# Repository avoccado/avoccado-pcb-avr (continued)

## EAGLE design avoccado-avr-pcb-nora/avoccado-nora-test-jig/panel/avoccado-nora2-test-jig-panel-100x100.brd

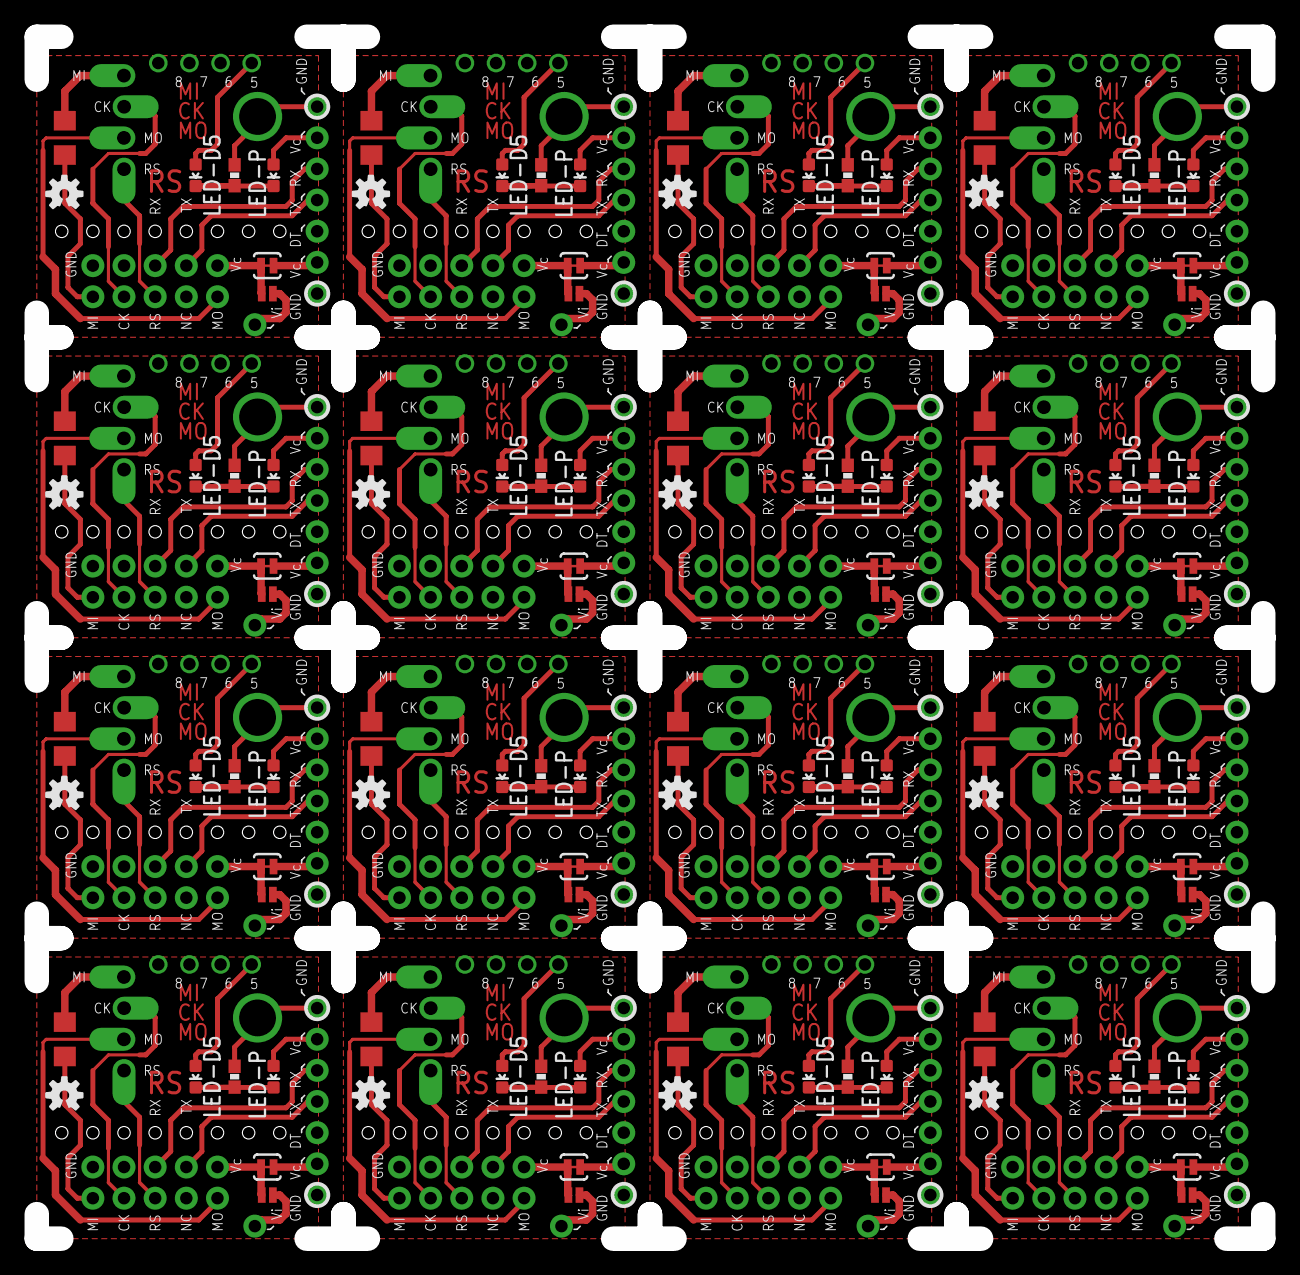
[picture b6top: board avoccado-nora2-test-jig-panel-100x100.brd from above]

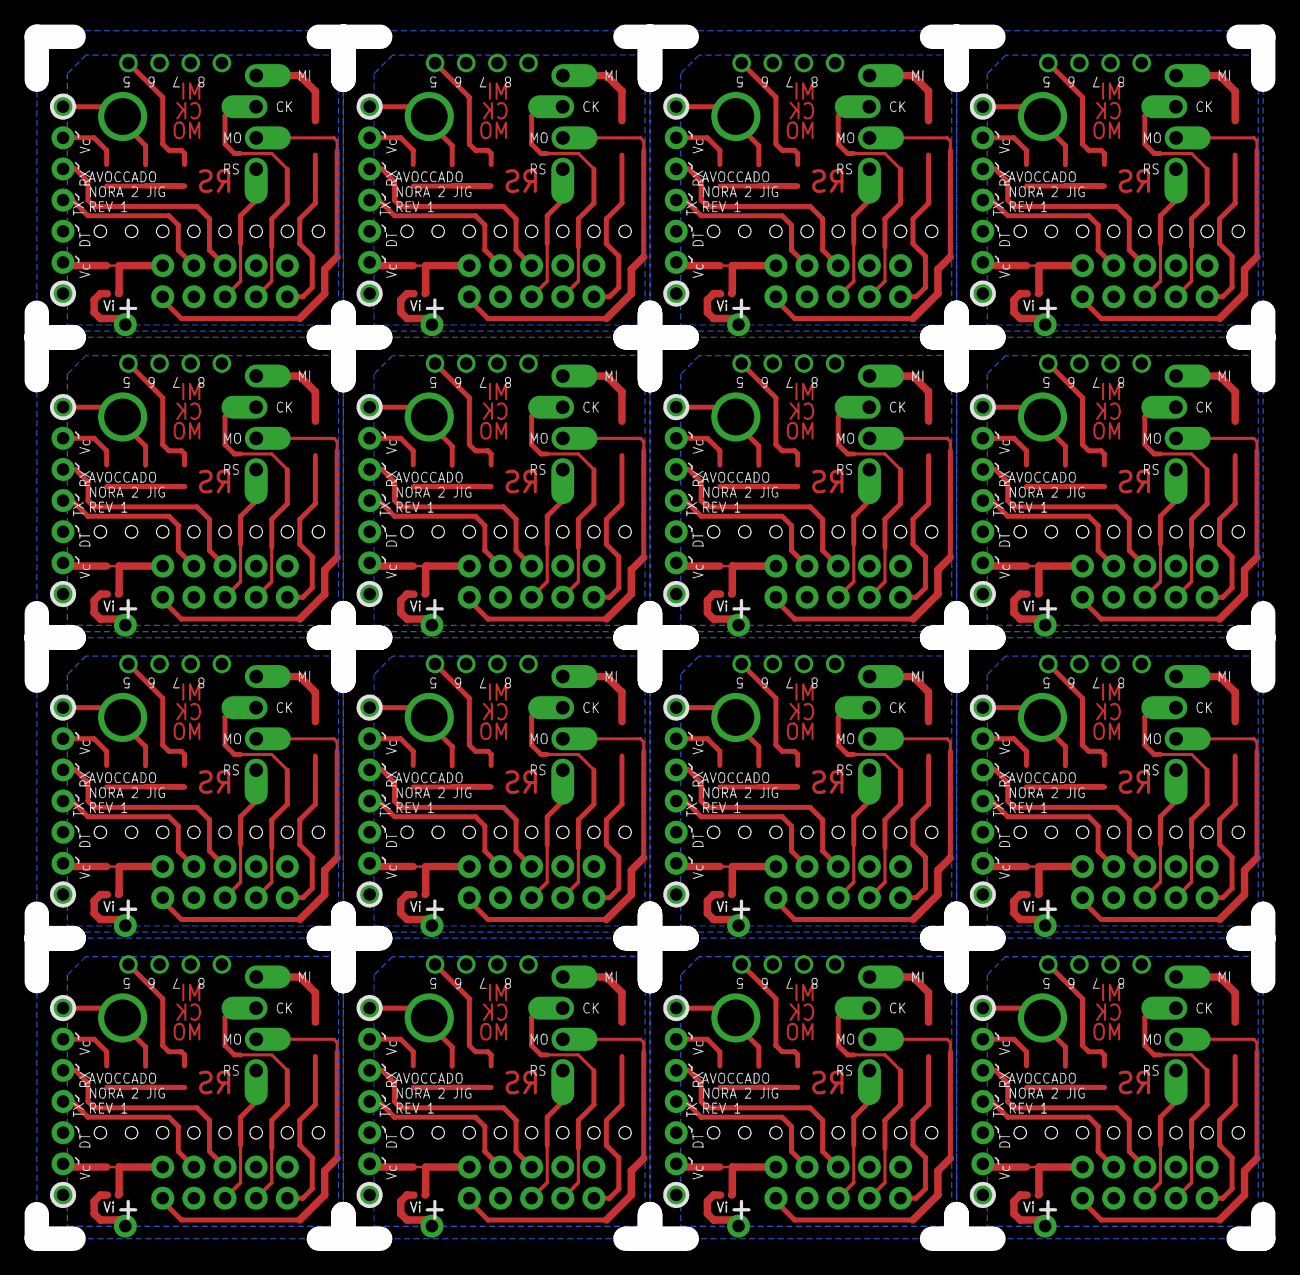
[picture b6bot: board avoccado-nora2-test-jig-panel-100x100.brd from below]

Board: 2 copper layers, 100.0 x 98.0 mm, 384 parts (16 on the bottom side), 224 nets.

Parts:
D5-LED, D5-LED1, D5-LED2, D5-LED3, D5-LED4, D5-LED5, D5-LED6, D5-LED7, D5-LED8, D5-LED9, D5-LED10, D5-LED11, D5-LED12, D5-LED13, D5-LED14, D5-LED15: LED-0603
ICSP, ICSP1, ICSP2, ICSP3, ICSP4, ICSP5, ICSP6, ICSP7, ICSP8, ICSP9, ICSP10, ICSP11, ICSP12, ICSP13, ICSP14, ICSP15: M05X2NO_SILK; 2X5_NOSILK
JP1, JP2, JP3, JP4, JP5, JP6, JP7, JP8, JP9, JP10, JP11, JP17, JP18, JP22, JP23, JP24, JP25, JP26, JP27, JP28, JP29, JP34, JP35, JP36, JP37, JP38, JP39, JP40, JP41, JP46, JP47, JP48, JP49, JP50, JP51, JP52, JP53, JP58, JP59, JP60, JP61, JP62, JP63, JP64, JP65, JP70, JP71, JP72, JP73, JP74, JP75, JP76, JP77, JP82, JP83, JP84, JP85, JP86, JP87, JP88, JP89, JP94, JP95, JP96, JP97, JP98, JP99, JP100, JP101, JP106, JP107, JP108, JP109, JP110, JP111, JP112, JP113, JP118, JP119, JP120, JP121, JP122, JP123, JP124, JP125, JP130, JP131, JP132, JP133, JP134, JP135, JP136, JP137, JP142, JP143, JP144, JP145, JP146, JP147, JP148, JP149, JP154, JP155, JP156, JP157, JP158, JP159, JP160, JP161, JP166, JP167, JP168, JP169, JP170, JP171, JP172, JP173, JP178, JP179, JP180, JP181, JP182, JP183, JP184, JP185, JP190, JP191, JP192: M01PTH; 1X01
JP12, JP13, JP14, JP15, JP16, JP19, JP20, JP21, JP30, JP31, JP32, JP33, JP42, JP43, JP44, JP45, JP54, JP55, JP56, JP57, JP66, JP67, JP68, JP69, JP78, JP79, JP80, JP81, JP90, JP91, JP92, JP93, JP102, JP103, JP104, JP105, JP114, JP115, JP116, JP117, JP126, JP127, JP128, JP129, JP138, JP139, JP140, JP141, JP150, JP151, JP152, JP153, JP162, JP163, JP164, JP165, JP174, JP175, JP176, JP177, JP186, JP187, JP188, JP189: M01OFFSET; 1X01_OFFSET
LOGO1, LOGO2, LOGO3, LOGO4, LOGO5, LOGO6, LOGO7, LOGO8, LOGO9, LOGO10, LOGO11, LOGO12, LOGO13, LOGO14, LOGO15, LOGO16: OSHW-LOGOS; OSHW-LOGO-S
PWR-LED, PWR-LED1, PWR-LED2, PWR-LED3, PWR-LED4, PWR-LED5, PWR-LED6, PWR-LED7, PWR-LED8, PWR-LED9, PWR-LED10, PWR-LED11, PWR-LED12, PWR-LED13, PWR-LED14, PWR-LED15: LED-0603
R1, R3, R5, R7, R9, R11, R13, R15, R17, R19, R21, R23, R25, R27, R29, R31: 0; 1206
R2, R4, R6, R8, R10, R12, R14, R16, R18, R20, R22, R24, R26, R28, R30, R32: 1K; 0603-RES
SJ1, SJ3, SJ5, SJ7, SJ9, SJ11, SJ13, SJ15, SJ17, SJ19, SJ21, SJ23, SJ25, SJ27, SJ29, SJ31: JUMPER-PAD-2-NC_BY_TRACE; PAD-JUMPER-2-NC_BY_TRACE_YES_SILK
SJ2, SJ4, SJ6, SJ8, SJ10, SJ12, SJ14, SJ16, SJ18, SJ20, SJ22, SJ24, SJ26, SJ28, SJ30, SJ32: JUMPER-PAD-2-NO; PAD-JUMPER-2-NO_NO_SILK
TP1, TP2, TP3, TP4, TP5, TP6, TP7, TP8, TP9, TP10, TP11, TP12, TP13, TP14, TP15, TP16, TP17, TP18, TP19, TP20, TP21, TP22, TP23, TP24, TP25, TP26, TP27, TP28, TP29, TP30, TP31, TP32, TP33, TP34, TP35, TP36, TP37, TP38, TP39, TP40, TP41, TP42, TP43, TP44, TP45, TP46, TP47, TP48, TP49, TP50, TP51, TP52, TP53, TP54, TP55, TP56, TP57, TP58, TP59, TP60, TP61, TP62, TP63, TP64: M01NOSILK-KIT; 1X01NS-KIT

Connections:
3.3V: JP18.1, SJ1.1
3.3V1: JP24.1, SJ3.1
3.3V2: JP36.1, SJ5.1
3.3V3: JP48.1, SJ7.1
3.3V4: JP60.1, SJ9.1
3.3V5: JP72.1, SJ11.1
3.3V6: JP84.1, SJ13.1
3.3V7: JP96.1, SJ15.1
3.3V8: JP108.1, SJ17.1
3.3V9: JP120.1, SJ19.1
3.3V10: JP132.1, SJ21.1
3.3V11: JP144.1, SJ23.1
3.3V12: JP156.1, SJ25.1
3.3V13: JP168.1, SJ27.1
3.3V14: JP180.1, SJ29.1
3.3V15: JP192.1, SJ31.1
5V: JP17.1, SJ2.1
5V1: JP23.1, SJ4.1
5V2: JP35.1, SJ6.1
5V3: JP47.1, SJ8.1
5V4: JP59.1, SJ10.1
5V5: JP71.1, SJ12.1
5V6: JP83.1, SJ14.1
5V7: JP95.1, SJ16.1
5V8: JP107.1, SJ18.1
5V9: JP119.1, SJ20.1
5V10: JP131.1, SJ22.1
5V11: JP143.1, SJ24.1
5V12: JP155.1, SJ26.1
5V13: JP167.1, SJ28.1
5V14: JP179.1, SJ30.1
5V15: JP191.1, SJ32.1
D2: D5-LED1.A, TP2.1
D5: D5-LED.A, TP1.1
D10: D5-LED2.A, TP9.1
D14: D5-LED3.A, TP13.1
D18: D5-LED4.A, TP17.1
D22: D5-LED5.A, TP21.1
D26: D5-LED6.A, TP25.1
D30: D5-LED7.A, TP29.1
D34: D5-LED8.A, TP33.1
D38: D5-LED9.A, TP37.1
D42: D5-LED10.A, TP41.1
D46: D5-LED11.A, TP45.1
D50: D5-LED12.A, TP49.1
D54: D5-LED13.A, TP53.1
D58: D5-LED14.A, TP57.1
D62: D5-LED15.A, TP61.1
GND: ICSP.10, JP3.1, JP6.1, R2.2
GND1: ICSP1.10, JP1.1, JP22.1, R4.2
GND2: ICSP2.10, JP25.1, JP34.1, R6.2
GND3: ICSP3.10, JP37.1, JP46.1, R8.2
GND4: ICSP4.10, JP49.1, JP58.1, R10.2
GND5: ICSP5.10, JP61.1, JP70.1, R12.2
GND6: ICSP6.10, JP73.1, JP82.1, R14.2
GND7: ICSP7.10, JP85.1, JP94.1, R16.2
GND8: ICSP8.10, JP97.1, JP106.1, R18.2
GND9: ICSP9.10, JP109.1, JP118.1, R20.2
GND10: ICSP10.10, JP121.1, JP130.1, R22.2
GND11: ICSP11.10, JP133.1, JP142.1, R24.2
GND12: ICSP12.10, JP145.1, JP154.1, R26.2
GND13: ICSP13.10, JP157.1, JP166.1, R28.2
GND14: ICSP14.10, JP169.1, JP178.1, R30.2
GND15: ICSP15.10, JP181.1, JP190.1, R32.2
MISO: JP12.1, R1.1
MISO1: ICSP.9, R1.2
MISO2: JP16.1, R3.1
MISO3: ICSP1.9, R3.2
MISO4: JP30.1, R5.1
MISO5: ICSP2.9, R5.2
MISO6: JP42.1, R7.1
MISO7: ICSP3.9, R7.2
MISO8: JP54.1, R9.1
MISO9: ICSP4.9, R9.2
MISO10: JP66.1, R11.1
MISO11: ICSP5.9, R11.2
MISO12: JP78.1, R13.1
MISO13: ICSP6.9, R13.2
MISO14: JP90.1, R15.1
MISO15: ICSP7.9, R15.2
MISO16: JP102.1, R17.1
MISO17: ICSP8.9, R17.2
MISO18: JP114.1, R19.1
MISO19: ICSP9.9, R19.2
MISO20: JP126.1, R21.1
MISO21: ICSP10.9, R21.2
MISO22: JP138.1, R23.1
MISO23: ICSP11.9, R23.2
MISO24: JP150.1, R25.1
MISO25: ICSP12.9, R25.2
MISO26: JP162.1, R27.1
MISO27: ICSP13.9, R27.2
MISO28: JP174.1, R29.1
MISO29: ICSP14.9, R29.2
MISO30: JP186.1, R31.1
MISO31: ICSP15.9, R31.2
MOSI: ICSP.1, JP14.1
MOSI1: ICSP1.1, JP20.1
MOSI2: ICSP2.1, JP32.1
MOSI3: ICSP3.1, JP44.1
MOSI4: ICSP4.1, JP56.1
MOSI5: ICSP5.1, JP68.1
MOSI6: ICSP6.1, JP80.1
MOSI7: ICSP7.1, JP92.1
MOSI8: ICSP8.1, JP104.1
MOSI9: ICSP9.1, JP116.1
MOSI10: ICSP10.1, JP128.1
MOSI11: ICSP11.1, JP140.1
MOSI12: ICSP12.1, JP152.1
MOSI13: ICSP13.1, JP164.1
MOSI14: ICSP14.1, JP176.1
MOSI15: ICSP15.1, JP188.1
unnamed: D5-LED.C, PWR-LED.C, R2.1
unnamed: JP11.1, PWR-LED.A
unnamed: D5-LED1.C, PWR-LED1.C, R4.1
unnamed: JP7.1, PWR-LED1.A
unnamed: D5-LED2.C, PWR-LED2.C, R6.1
unnamed: JP29.1, PWR-LED2.A
unnamed: D5-LED3.C, PWR-LED3.C, R8.1
unnamed: JP41.1, PWR-LED3.A
unnamed: D5-LED4.C, PWR-LED4.C, R10.1
unnamed: JP53.1, PWR-LED4.A
unnamed: D5-LED5.C, PWR-LED5.C, R12.1
unnamed: JP65.1, PWR-LED5.A
unnamed: D5-LED6.C, PWR-LED6.C, R14.1
unnamed: JP77.1, PWR-LED6.A
unnamed: D5-LED7.C, PWR-LED7.C, R16.1
unnamed: JP89.1, PWR-LED7.A
unnamed: D5-LED8.C, PWR-LED8.C, R18.1
unnamed: JP101.1, PWR-LED8.A
unnamed: D5-LED9.C, PWR-LED9.C, R20.1
unnamed: JP113.1, PWR-LED9.A
unnamed: D5-LED10.C, PWR-LED10.C, R22.1
unnamed: JP125.1, PWR-LED10.A
unnamed: D5-LED11.C, PWR-LED11.C, R24.1
unnamed: JP137.1, PWR-LED11.A
unnamed: D5-LED12.C, PWR-LED12.C, R26.1
unnamed: JP149.1, PWR-LED12.A
unnamed: D5-LED13.C, PWR-LED13.C, R28.1
unnamed: JP161.1, PWR-LED13.A
unnamed: D5-LED14.C, PWR-LED14.C, R30.1
unnamed: JP173.1, PWR-LED14.A
unnamed: D5-LED15.C, PWR-LED15.C, R32.1
unnamed: JP185.1, PWR-LED15.A
RESET: ICSP.5, JP15.1
RESET1: ICSP1.5, JP21.1
RESET2: ICSP2.5, JP33.1
RESET3: ICSP3.5, JP45.1
RESET4: ICSP4.5, JP57.1
RESET5: ICSP5.5, JP69.1
RESET6: ICSP6.5, JP81.1
RESET7: ICSP7.5, JP93.1
RESET8: ICSP8.5, JP105.1
RESET9: ICSP9.5, JP117.1
RESET10: ICSP10.5, JP129.1
RESET11: ICSP11.5, JP141.1
RESET12: ICSP12.5, JP153.1
RESET13: ICSP13.5, JP165.1
RESET14: ICSP14.5, JP177.1
RESET15: ICSP15.5, JP189.1
RXI: ICSP.6, JP8.1
RXI1: ICSP1.6, JP2.1
RXI2: ICSP2.6, JP26.1
RXI3: ICSP3.6, JP38.1
RXI4: ICSP4.6, JP50.1
RXI5: ICSP5.6, JP62.1
RXI6: ICSP6.6, JP74.1
RXI7: ICSP7.6, JP86.1
RXI8: ICSP8.6, JP98.1
RXI9: ICSP9.6, JP110.1
RXI10: ICSP10.6, JP122.1
RXI11: ICSP11.6, JP134.1
RXI12: ICSP12.6, JP146.1
RXI13: ICSP13.6, JP158.1
RXI14: ICSP14.6, JP170.1
RXI15: ICSP15.6, JP182.1
SCK: ICSP.7, JP13.1
SCK1: ICSP1.7, JP19.1
SCK2: ICSP2.7, JP31.1
SCK3: ICSP3.7, JP43.1
SCK4: ICSP4.7, JP55.1
SCK5: ICSP5.7, JP67.1
SCK6: ICSP6.7, JP79.1
SCK7: ICSP7.7, JP91.1
SCK8: ICSP8.7, JP103.1
SCK9: ICSP9.7, JP115.1
SCK10: ICSP10.7, JP127.1
SCK11: ICSP11.7, JP139.1
SCK12: ICSP12.7, JP151.1
SCK13: ICSP13.7, JP163.1
SCK14: ICSP14.7, JP175.1
SCK15: ICSP15.7, JP187.1
TXO: ICSP.4, JP9.1
TXO1: ICSP1.4, JP4.1
TXO2: ICSP2.4, JP27.1
TXO3: ICSP3.4, JP39.1
TXO4: ICSP4.4, JP51.1
TXO5: ICSP5.4, JP63.1
TXO6: ICSP6.4, JP75.1
TXO7: ICSP7.4, JP87.1
TXO8: ICSP8.4, JP99.1
TXO9: ICSP9.4, JP111.1
TXO10: ICSP10.4, JP123.1
TXO11: ICSP11.4, JP135.1
TXO12: ICSP12.4, JP147.1
TXO13: ICSP13.4, JP159.1
TXO14: ICSP14.4, JP171.1
TXO15: ICSP15.4, JP183.1
VTG: ICSP.2, SJ1.2, SJ2.2
VTG1: ICSP1.2, SJ3.2, SJ4.2
VTG2: ICSP2.2, SJ5.2, SJ6.2
VTG3: ICSP3.2, SJ7.2, SJ8.2
VTG4: ICSP4.2, SJ9.2, SJ10.2
VTG5: ICSP5.2, SJ11.2, SJ12.2
VTG6: ICSP6.2, SJ13.2, SJ14.2
VTG7: ICSP7.2, SJ15.2, SJ16.2
VTG8: ICSP8.2, SJ17.2, SJ18.2
VTG9: ICSP9.2, SJ19.2, SJ20.2
VTG10: ICSP10.2, SJ21.2, SJ22.2
VTG11: ICSP11.2, SJ23.2, SJ24.2
VTG12: ICSP12.2, SJ25.2, SJ26.2
VTG13: ICSP13.2, SJ27.2, SJ28.2
VTG14: ICSP14.2, SJ29.2, SJ30.2
VTG15: ICSP15.2, SJ31.2, SJ32.2
